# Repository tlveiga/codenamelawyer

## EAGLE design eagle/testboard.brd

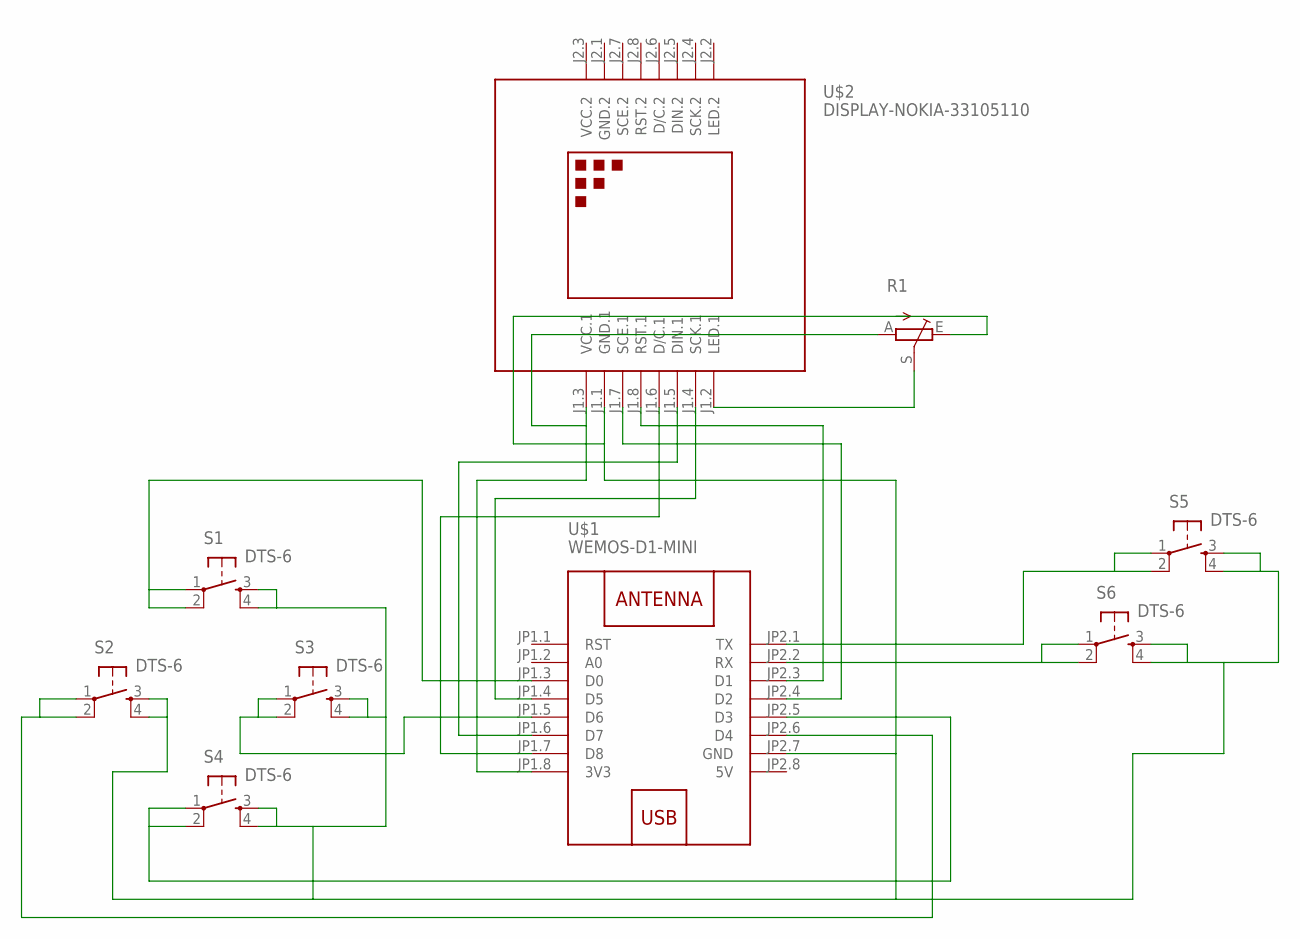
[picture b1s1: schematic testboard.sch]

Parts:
R1: TRIM_EU-B25U; B25U
S1, S2, S3, S4, S5, S6: DTS-6
U$1: WEMOS-D1-MINI
U$2: DISPLAY-NOKIA-33105110; DISPLAY-NOKIA-3310

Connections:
5V: U$1.JP2.8 (5V)
GND.2: U$2.J2.1 (GND.2)
unnamed: R1.A, U$1.JP1.8 (3V3), U$2.J1.3 (VCC.1)
unnamed: R1.E, S1.3, S1.4, S2.3, S2.4, S3.3, S3.4, S4.3, S4.4, S5.3, S5.4, S6.3, S6.4, U$1.JP2.7 (GND), U$2.J1.1 (GND.1)
unnamed: S1.1, S1.2, U$1.JP1.3 (D0)
unnamed: U$1.JP1.4 (D5), U$2.J1.4 (SCK.1)
unnamed: U$1.JP2.3 (D1), U$2.J1.8 (RST.1)
unnamed: U$1.JP1.6 (D7), U$2.J1.5 (DIN.1)
unnamed: U$1.JP2.4 (D2), U$2.J1.7 (SCE.1)
unnamed: R1.S, U$2.J1.2 (LED.1)
unnamed: S3.1, S3.2, U$1.JP1.5 (D6)
unnamed: S2.1, S2.2, U$1.JP2.6 (D4)
unnamed: S4.1, S4.2, U$1.JP2.5 (D3)
unnamed: S6.1, S6.2, U$1.JP2.2 (RX)
unnamed: S5.1, S5.2, U$1.JP2.1 (TX)
unnamed: U$1.JP1.7 (D8), U$2.J1.6 (D/C.1)
VCC.2: U$2.J2.3 (VCC.2)

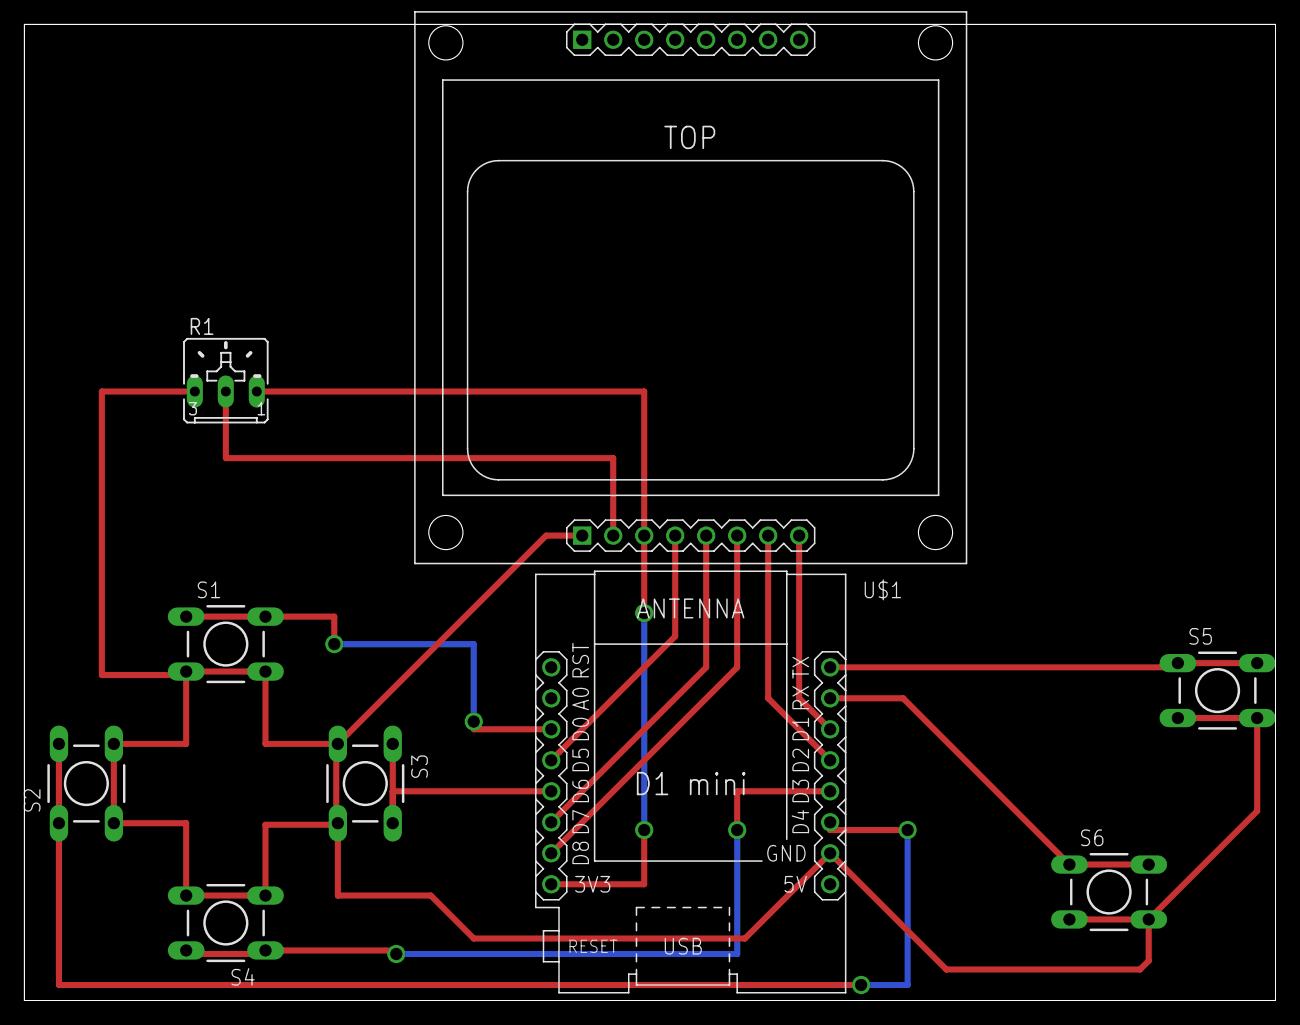
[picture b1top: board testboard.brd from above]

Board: 2 copper layers, 102.5 x 80.0 mm, 9 parts (0 on the bottom side), 14 nets.

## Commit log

2018-02-09 Skel
2018-02-10 More classes and eagle test board
2018-02-24 Some changes

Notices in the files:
parts and their libraries:
diy-modules: Released under the Creative Commons Attribution 4.0 International License: http://creativecommons.org/licenses/by/4.0
